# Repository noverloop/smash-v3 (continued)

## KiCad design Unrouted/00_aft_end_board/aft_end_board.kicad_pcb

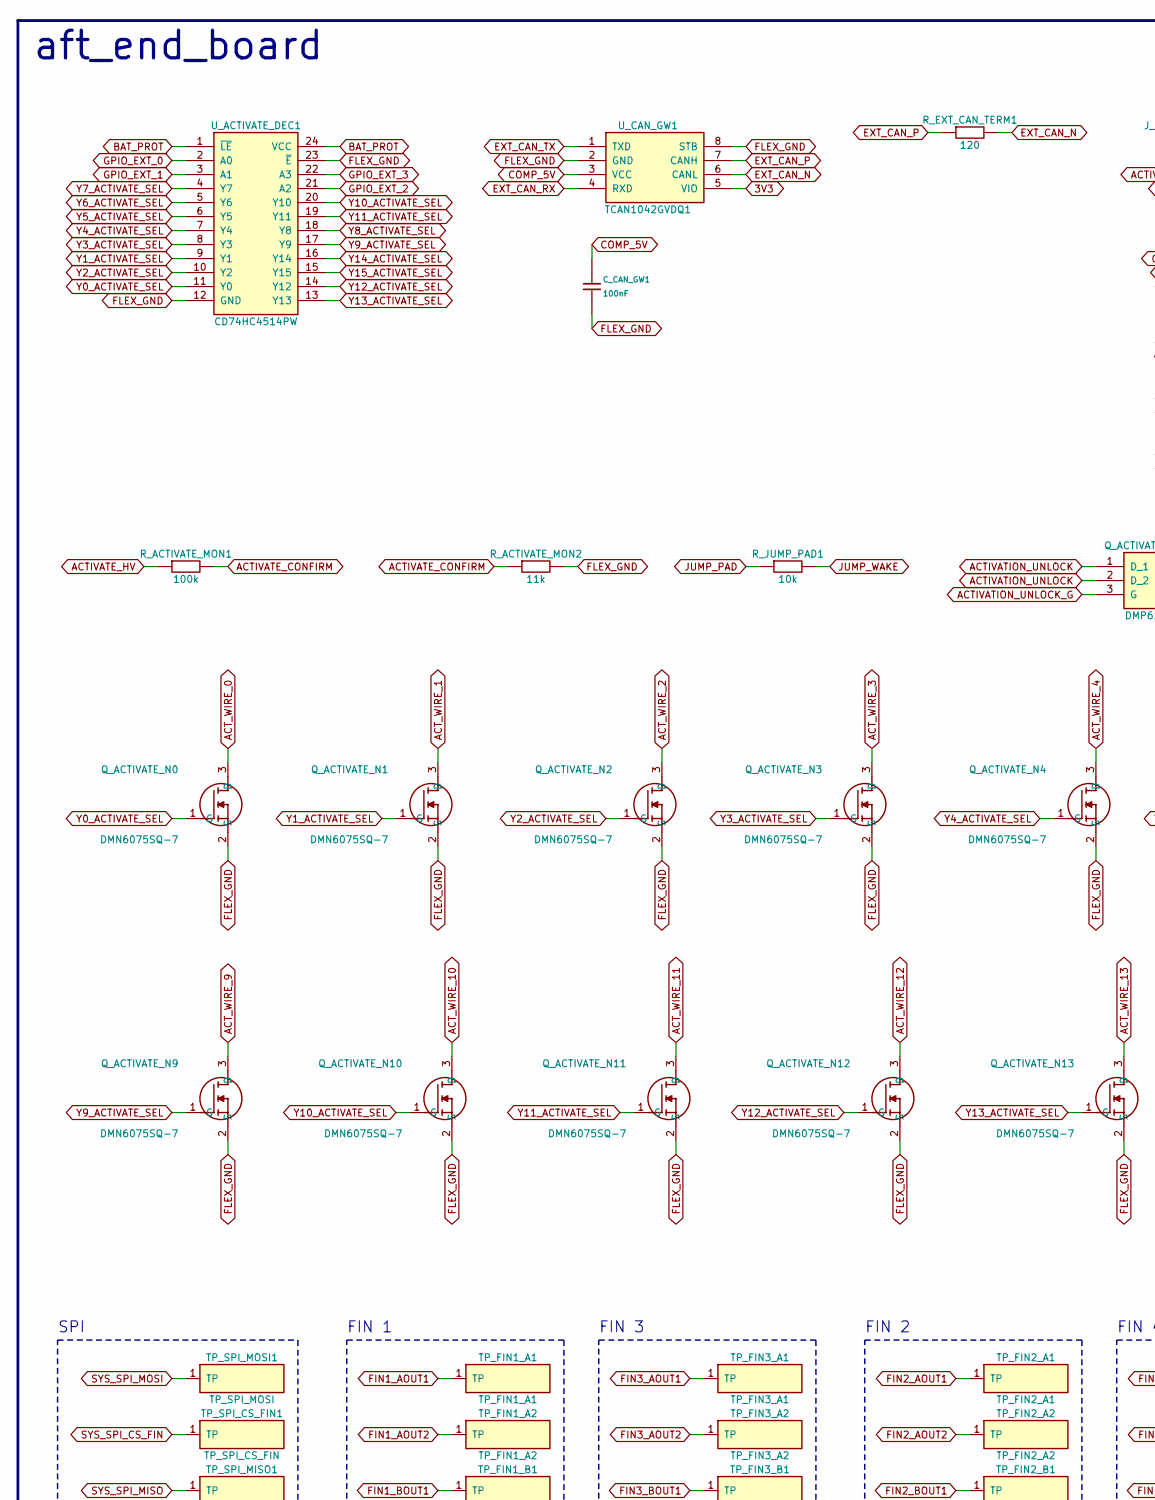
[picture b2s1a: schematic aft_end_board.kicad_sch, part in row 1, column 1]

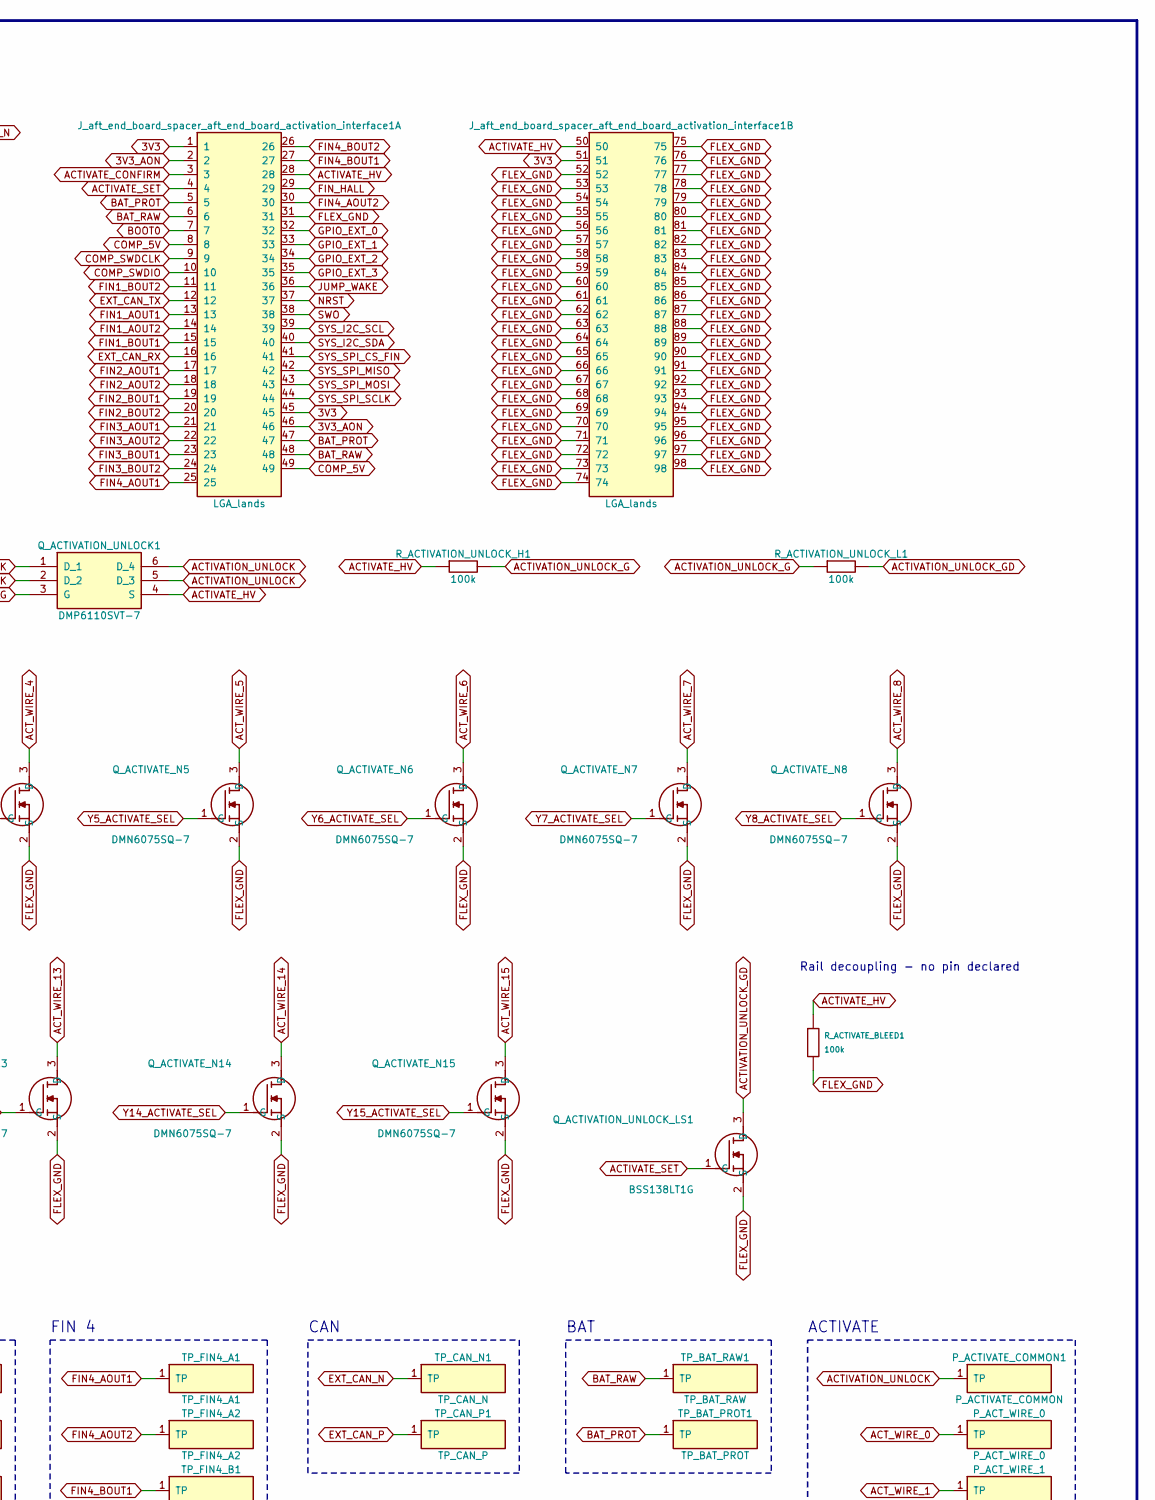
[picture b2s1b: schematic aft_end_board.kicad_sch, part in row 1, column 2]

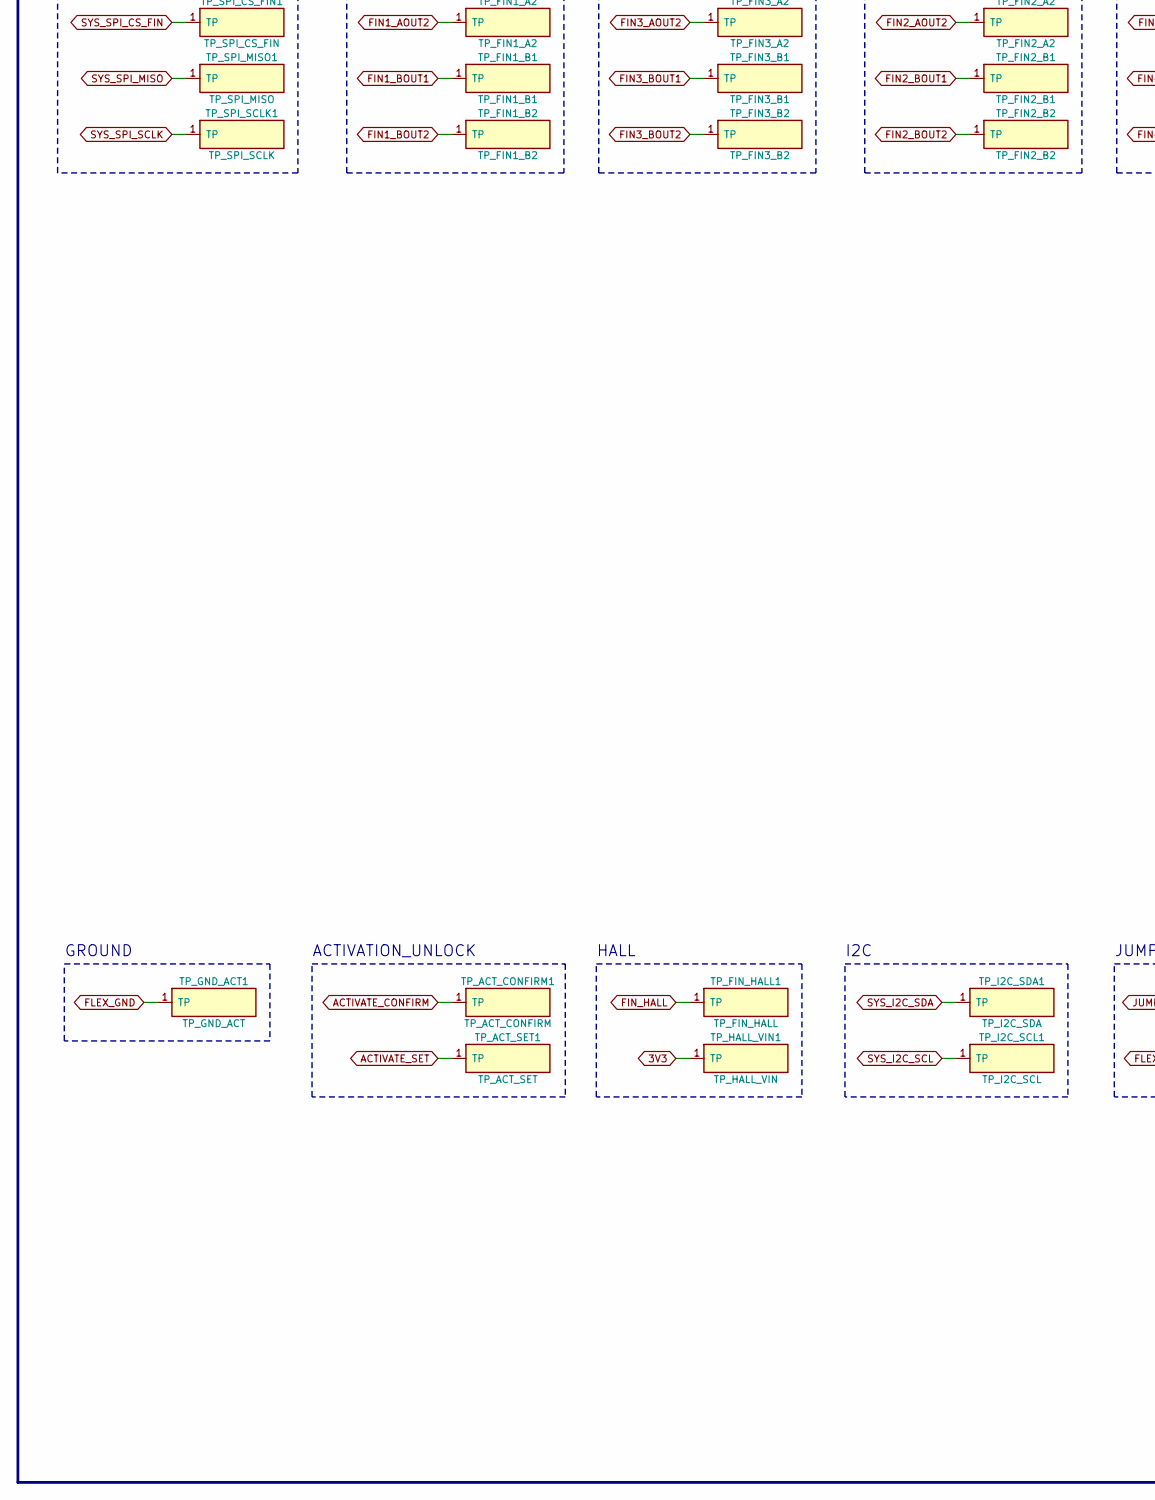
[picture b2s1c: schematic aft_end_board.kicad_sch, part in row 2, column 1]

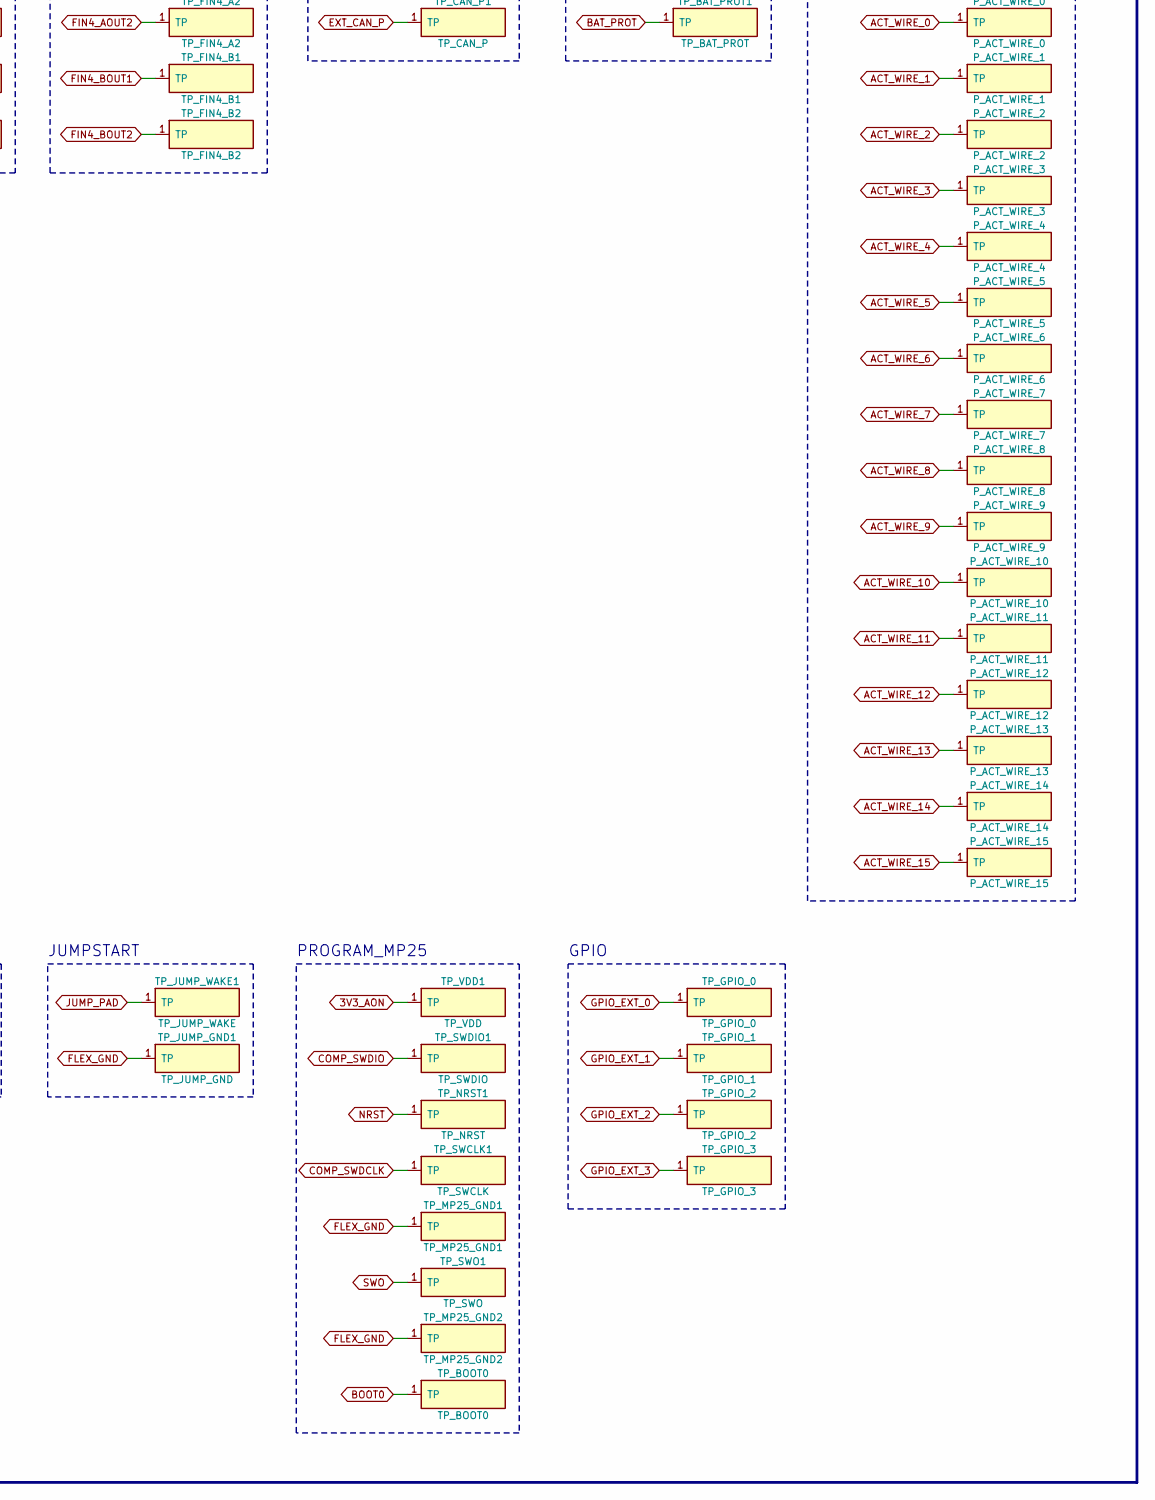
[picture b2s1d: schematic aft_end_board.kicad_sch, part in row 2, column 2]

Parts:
C_CAN_GW1: 100nF; Capacitor_SMD_C_0402_1005Metric; MPN C0402 X7R 100nF
J_aft_end_board_spacer_aft_end_board_activation_interface1: LGA_lands; J_aft_end_board_spacer_aft_end_board_activation_interface; MPN LGA_lands
P_ACTIVATE_COMMON1: P_ACTIVATE_COMMON; Pogo_Pad_D2.0mm
P_ACT_WIRE_0: P_ACT_WIRE_0; Pogo_Pad_S2.0mm
P_ACT_WIRE_1: P_ACT_WIRE_1; Pogo_Pad_D2.0mm
P_ACT_WIRE_2: P_ACT_WIRE_2; Pogo_Pad_D2.0mm
P_ACT_WIRE_3: P_ACT_WIRE_3; Pogo_Pad_D2.0mm
P_ACT_WIRE_4: P_ACT_WIRE_4; Pogo_Pad_D2.0mm
P_ACT_WIRE_5: P_ACT_WIRE_5; Pogo_Pad_D2.0mm
P_ACT_WIRE_6: P_ACT_WIRE_6; Pogo_Pad_D2.0mm
P_ACT_WIRE_7: P_ACT_WIRE_7; Pogo_Pad_D2.0mm
P_ACT_WIRE_8: P_ACT_WIRE_8; Pogo_Pad_D2.0mm
P_ACT_WIRE_9: P_ACT_WIRE_9; Pogo_Pad_D2.0mm
P_ACT_WIRE_10: P_ACT_WIRE_10; Pogo_Pad_D2.0mm
P_ACT_WIRE_11: P_ACT_WIRE_11; Pogo_Pad_D2.0mm
P_ACT_WIRE_12: P_ACT_WIRE_12; Pogo_Pad_D2.0mm
P_ACT_WIRE_13: P_ACT_WIRE_13; Pogo_Pad_D2.0mm
P_ACT_WIRE_14: P_ACT_WIRE_14; Pogo_Pad_D2.0mm
P_ACT_WIRE_15: P_ACT_WIRE_15; Pogo_Pad_D2.0mm
Q_ACTIVATE_N0, Q_ACTIVATE_N1, Q_ACTIVATE_N2, Q_ACTIVATE_N3, Q_ACTIVATE_N4, Q_ACTIVATE_N5, Q_ACTIVATE_N6, Q_ACTIVATE_N7, Q_ACTIVATE_N8, Q_ACTIVATE_N9, Q_ACTIVATE_N10, Q_ACTIVATE_N11, Q_ACTIVATE_N12, Q_ACTIVATE_N13, Q_ACTIVATE_N14, Q_ACTIVATE_N15: DMN6075SQ-7; SOT96P240X110-3N; MPN DMN6075SQ-7
Q_ACTIVATION_UNLOCK1: DMP6110SVT-7; SOT95P280X100-6N; MPN DMP6110SVT-7
Q_ACTIVATION_UNLOCK_LS1: BSS138LT1G; SOT96P237X111-3N; MPN BSS138LT1G
R_ACTIVATE_BLEED1: 100k; Resistor_SMD_R_0402_1005Metric; MPN CRCW0402 100k 1% e3
R_ACTIVATE_MON1: 100k; Resistor_SMD_R_0402_1005Metric; MPN CRCW0402 100k 1% e3
R_ACTIVATE_MON2: 11k; Resistor_SMD_R_0402_1005Metric; MPN CRCW0402 11k 1% e3
R_ACTIVATION_UNLOCK_H1: 100k; Resistor_SMD_R_0402_1005Metric; MPN CRCW0402 100k 1% e3
R_ACTIVATION_UNLOCK_L1: 100k; Resistor_SMD_R_0402_1005Metric; MPN CRCW0402 100k 1% e3
R_EXT_CAN_TERM1: 120; Resistor_SMD_R_0402_1005Metric; MPN CRCW0402 120 1% e3
R_JUMP_PAD1: 10k; Resistor_SMD_R_0402_1005Metric; MPN CRCW0402 10k 1% e3
TP_ACT_CONFIRM1: TP_ACT_CONFIRM; Pogo_Pad_S2.0mm
TP_ACT_SET1: TP_ACT_SET; Pogo_Pad_D2.0mm
TP_BAT_PROT1: TP_BAT_PROT; Pogo_Pad_D2.0mm
TP_BAT_RAW1: TP_BAT_RAW; Pogo_Pad_S2.0mm
TP_BOOT0: TP_BOOT0; Pogo_Pad_D2.0mm
TP_CAN_N1: TP_CAN_N; Pogo_Pad_S2.0mm
TP_CAN_P1: TP_CAN_P; Pogo_Pad_D2.0mm
TP_FIN1_A1: TP_FIN1_A1; Pogo_Pad_S2.0mm
TP_FIN1_A2: TP_FIN1_A2; Pogo_Pad_D2.0mm
TP_FIN1_B1: TP_FIN1_B1; Pogo_Pad_D2.0mm
TP_FIN1_B2: TP_FIN1_B2; Pogo_Pad_D2.0mm
TP_FIN2_A1: TP_FIN2_A1; Pogo_Pad_S2.0mm
TP_FIN2_A2: TP_FIN2_A2; Pogo_Pad_D2.0mm
TP_FIN2_B1: TP_FIN2_B1; Pogo_Pad_D2.0mm
TP_FIN2_B2: TP_FIN2_B2; Pogo_Pad_D2.0mm
TP_FIN3_A1: TP_FIN3_A1; Pogo_Pad_S2.0mm
TP_FIN3_A2: TP_FIN3_A2; Pogo_Pad_D2.0mm
TP_FIN3_B1: TP_FIN3_B1; Pogo_Pad_D2.0mm
TP_FIN3_B2: TP_FIN3_B2; Pogo_Pad_D2.0mm
TP_FIN4_A1: TP_FIN4_A1; Pogo_Pad_S2.0mm
TP_FIN4_A2: TP_FIN4_A2; Pogo_Pad_D2.0mm
TP_FIN4_B1: TP_FIN4_B1; Pogo_Pad_D2.0mm
TP_FIN4_B2: TP_FIN4_B2; Pogo_Pad_D2.0mm
TP_FIN_HALL1: TP_FIN_HALL; Pogo_Pad_S2.0mm
TP_GND_ACT1: TP_GND_ACT; Pogo_Pad_D2.0mm
TP_GPIO_0: TP_GPIO_0; Pogo_Pad_S2.0mm
TP_GPIO_1: TP_GPIO_1; Pogo_Pad_D2.0mm
TP_GPIO_2: TP_GPIO_2; Pogo_Pad_D2.0mm
TP_GPIO_3: TP_GPIO_3; Pogo_Pad_D2.0mm
TP_HALL_VIN1: TP_HALL_VIN; Pogo_Pad_D2.0mm
TP_I2C_SCL1: TP_I2C_SCL; Pogo_Pad_D2.0mm
TP_I2C_SDA1: TP_I2C_SDA; Pogo_Pad_S2.0mm
TP_JUMP_GND1: TP_JUMP_GND; Pogo_Pad_D2.0mm
TP_JUMP_WAKE1: TP_JUMP_WAKE; Pogo_Pad_S2.0mm
TP_MP25_GND1: TP_MP25_GND1; Pogo_Pad_D2.0mm
TP_MP25_GND2: TP_MP25_GND2; Pogo_Pad_D2.0mm
TP_NRST1: TP_NRST; Pogo_Pad_D2.0mm
TP_SPI_CS_FIN1: TP_SPI_CS_FIN; Pogo_Pad_D2.0mm
TP_SPI_MISO1: TP_SPI_MISO; Pogo_Pad_D2.0mm
TP_SPI_MOSI1: TP_SPI_MOSI; Pogo_Pad_S2.0mm
TP_SPI_SCLK1: TP_SPI_SCLK; Pogo_Pad_D2.0mm
TP_SWCLK1: TP_SWCLK; Pogo_Pad_D2.0mm
TP_SWDIO1: TP_SWDIO; Pogo_Pad_D2.0mm
TP_SWO1: TP_SWO; Pogo_Pad_D2.0mm
TP_VDD1: TP_VDD; Pogo_Pad_S2.0mm
U_ACTIVATE_DEC1: CD74HC4514PW; SOP65P640X120-24N; MPN CD74HC4514PW
U_CAN_GW1: TCAN1042GVDQ1; SOIC127P600X175-8N; MPN TCAN1042GVDQ1

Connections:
3V3: J_aft_end_board_spacer_aft_end_board_ac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.1, J_aft_end_board_spacer_aft_end_board_ac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.45, J_aft_end_board_spacer_aft_end_board_ac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.51, TP_HALL_VIN1.1, U_CAN_GW1.5 (VIO)
3V3_AON: J_aft_end_board_spacer_aft_end_board_ac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.2, J_aft_end_board_spacer_aft_end_board_ac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.46, TP_VDD1.1
ACTIVATE_CONFIRM: J_aft_end_board_spacer_aft_end_board_ac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.3, R_ACTIVATE_MON1.2, R_ACTIVATE_MON2.1, TP_ACT_CONFIRM1.1
ACTIVATE_HV: J_aft_end_board_spacer_aft_end_board_ac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.28, J_aft_end_board_spacer_aft_end_board_ac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.50, Q_ACTIVATION_UNLOCK1.4 (S), R_ACTIVATE_BLEED1.1, R_ACTIVATE_MON1.1, R_ACTIVATION_UNLOCK_H1.1
ACTIVATE_SET: J_aft_end_board_spacer_aft_end_board_ac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.4, Q_ACTIVATION_UNLOCK_LS1.1 (G), TP_ACT_SET1.1
ACTIVATION_UNLOCK: P_ACTIVATE_COMMON1.1, Q_ACTIVATION_UNLOCK1.1 (D_1), Q_ACTIVATION_UNLOCK1.2 (D_2), Q_ACTIVATION_UNLOCK1.5 (D_3), Q_ACTIVATION_UNLOCK1.6 (D_4)
ACTIVATION_UNLOCK_G: Q_ACTIVATION_UNLOCK1.3 (G), R_ACTIVATION_UNLOCK_H1.2, R_ACTIVATION_UNLOCK_L1.1
ACTIVATION_UNLOCK_GD: Q_ACTIVATION_UNLOCK_LS1.3 (D), R_ACTIVATION_UNLOCK_L1.2
ACT_WIRE_0: P_ACT_WIRE_0.1, Q_ACTIVATE_N0.3 (D)
ACT_WIRE_1: P_ACT_WIRE_1.1, Q_ACTIVATE_N1.3 (D)
ACT_WIRE_2: P_ACT_WIRE_2.1, Q_ACTIVATE_N2.3 (D)
ACT_WIRE_3: P_ACT_WIRE_3.1, Q_ACTIVATE_N3.3 (D)
ACT_WIRE_4: P_ACT_WIRE_4.1, Q_ACTIVATE_N4.3 (D)
ACT_WIRE_5: P_ACT_WIRE_5.1, Q_ACTIVATE_N5.3 (D)
ACT_WIRE_6: P_ACT_WIRE_6.1, Q_ACTIVATE_N6.3 (D)
ACT_WIRE_7: P_ACT_WIRE_7.1, Q_ACTIVATE_N7.3 (D)
ACT_WIRE_8: P_ACT_WIRE_8.1, Q_ACTIVATE_N8.3 (D)
ACT_WIRE_9: P_ACT_WIRE_9.1, Q_ACTIVATE_N9.3 (D)
ACT_WIRE_10: P_ACT_WIRE_10.1, Q_ACTIVATE_N10.3 (D)
ACT_WIRE_11: P_ACT_WIRE_11.1, Q_ACTIVATE_N11.3 (D)
ACT_WIRE_12: P_ACT_WIRE_12.1, Q_ACTIVATE_N12.3 (D)
ACT_WIRE_13: P_ACT_WIRE_13.1, Q_ACTIVATE_N13.3 (D)
ACT_WIRE_14: P_ACT_WIRE_14.1, Q_ACTIVATE_N14.3 (D)
ACT_WIRE_15: P_ACT_WIRE_15.1, Q_ACTIVATE_N15.3 (D)
BAT_PROT: J_aft_end_board_spacer_aft_end_board_ac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.5, J_aft_end_board_spacer_aft_end_board_ac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.47, TP_BAT_PROT1.1, U_ACTIVATE_DEC1.1 (~LE), U_ACTIVATE_DEC1.24 (VCC)
BAT_RAW: J_aft_end_board_spacer_aft_end_board_ac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.6, J_aft_end_board_spacer_aft_end_board_ac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.48, TP_BAT_RAW1.1
BOOT0: J_aft_end_board_spacer_aft_end_board_ac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.7, TP_BOOT0.1
COMP_5V: C_CAN_GW1.1, J_aft_end_board_spacer_aft_end_board_ac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.8, J_aft_end_board_spacer_aft_end_board_ac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.49, U_CAN_GW1.3 (VCC)
COMP_SWDCLK: J_aft_end_board_spacer_aft_end_board_ac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.9, TP_SWCLK1.1
COMP_SWDIO: J_aft_end_board_spacer_aft_end_board_ac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.10, TP_SWDIO1.1
EXT_CAN_N: R_EXT_CAN_TERM1.2, TP_CAN_N1.1, U_CAN_GW1.6 (CANL)
EXT_CAN_P: R_EXT_CAN_TERM1.1, TP_CAN_P1.1, U_CAN_GW1.7 (CANH)
EXT_CAN_RX: J_aft_end_board_spacer_aft_end_board_ac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.16, U_CAN_GW1.4 (RXD)
EXT_CAN_TX: J_aft_end_board_spacer_aft_end_board_ac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.12, U_CAN_GW1.1 (TXD)
FIN1_AOUT1: J_aft_end_board_spacer_aft_end_board_ac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.13, TP_FIN1_A1.1
FIN1_AOUT2: J_aft_end_board_spacer_aft_end_board_ac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.14, TP_FIN1_A2.1
FIN1_BOUT1: J_aft_end_board_spacer_aft_end_board_ac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.15, TP_FIN1_B1.1
FIN1_BOUT2: J_aft_end_board_spacer_aft_end_board_ac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.11, TP_FIN1_B2.1
FIN2_AOUT1: J_aft_end_board_spacer_aft_end_board_ac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.17, TP_FIN2_A1.1
FIN2_AOUT2: J_aft_end_board_spacer_aft_end_board_ac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.18, TP_FIN2_A2.1
FIN2_BOUT1: J_aft_end_board_spacer_aft_end_board_ac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.19, TP_FIN2_B1.1
FIN2_BOUT2: J_aft_end_board_spacer_aft_end_board_ac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.20, TP_FIN2_B2.1
FIN3_AOUT1: J_aft_end_board_spacer_aft_end_board_ac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.21, TP_FIN3_A1.1
FIN3_AOUT2: J_aft_end_board_spacer_aft_end_board_ac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.22, TP_FIN3_A2.1
FIN3_BOUT1: J_aft_end_board_spacer_aft_end_board_ac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.23, TP_FIN3_B1.1
FIN3_BOUT2: J_aft_end_board_spacer_aft_end_board_ac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.24, TP_FIN3_B2.1
FIN4_AOUT1: J_aft_end_board_spacer_aft_end_board_ac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.25, TP_FIN4_A1.1
FIN4_AOUT2: J_aft_end_board_spacer_aft_end_board_ac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.30, TP_FIN4_A2.1
FIN4_BOUT1: J_aft_end_board_spacer_aft_end_board_ac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.27, TP_FIN4_B1.1
FIN4_BOUT2: J_aft_end_board_spacer_aft_end_board_ac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.26, TP_FIN4_B2.1
FIN_HALL: J_aft_end_board_spacer_aft_end_board_ac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.29, TP_FIN_HALL1.1
FLEX_GND: C_CAN_GW1.2, J_aft_end_board_spacer_aft_end_board_ac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.31, J_aft_end_board_spacer_aft_end_board_ac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.52, J_aft_end_board_spacer_aft_end_board_ac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.53, J_aft_end_board_spacer_aft_end_board_ac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.54, J_aft_end_board_spacer_aft_end_board_ac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.55, J_aft_end_board_spacer_aft_end_board_ac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.56, J_aft_end_board_spacer_aft_end_board_ac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.57, J_aft_end_board_spacer_aft_end_board_ac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.58, J_aft_end_board_spacer_aft_end_board_ac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.59, J_aft_end_board_spacer_aft_end_board_ac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.60, J_aft_end_board_spacer_aft_end_board_ac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.61, J_aft_end_board_spacer_aft_end_board_ac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.62, J_aft_end_board_spacer_aft_end_board_ac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.63, J_aft_end_board_spacer_aft_end_board_ac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.64, J_aft_end_board_spacer_aft_end_board_ac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.65, J_aft_end_board_spacer_aft_end_board_ac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.66, J_aft_end_board_spacer_aft_end_board_ac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.67, J_aft_end_board_spacer_aft_end_board_ac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.68, J_aft_end_board_spacer_aft_end_board_ac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.69, J_aft_end_board_spacer_aft_end_board_ac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.70, J_aft_end_board_spacer_aft_end_board_ac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.71, J_aft_end_board_spacer_aft_end_board_ac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.72, J_aft_end_board_spacer_aft_end_board_ac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.73, J_aft_end_board_spacer_aft_end_board_ac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.74, J_aft_end_board_spacer_aft_end_board_ac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.75, J_aft_end_board_spacer_aft_end_board_ac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.76, J_aft_end_board_spacer_aft_end_board_ac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.77, J_aft_end_board_spacer_aft_end_board_ac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.78, J_aft_end_board_spacer_aft_end_board_ac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.79, J_aft_end_board_spacer_aft_end_board_ac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.80, J_aft_end_board_spacer_aft_end_board_ac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.81, J_aft_end_board_spacer_aft_end_board_ac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.82, J_aft_end_board_spacer_aft_end_board_ac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.83, J_aft_end_board_spacer_aft_end_board_ac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.84, J_aft_end_board_spacer_aft_end_board_ac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.85, J_aft_end_board_spacer_aft_end_board_ac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.86, J_aft_end_board_spacer_aft_end_board_ac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.87, J_aft_end_board_spacer_aft_end_board_ac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.88, J_aft_end_board_spacer_aft_end_board_ac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.89, J_aft_end_board_spacer_aft_end_board_ac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.90, J_aft_end_board_spacer_aft_end_board_ac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.91, J_aft_end_board_spacer_aft_end_board_ac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.92, J_aft_end_board_spacer_aft_end_board_ac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.93, J_aft_end_board_spacer_aft_end_board_ac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.94, J_aft_end_board_spacer_aft_end_board_ac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.95, J_aft_end_board_spacer_aft_end_board_ac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.96, J_aft_end_board_spacer_aft_end_board_ac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.97, J_aft_end_board_spacer_aft_end_board_ac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.98, Q_ACTIVATE_N0.2 (S), Q_ACTIVATE_N1.2 (S), Q_ACTIVATE_N2.2 (S), Q_ACTIVATE_N3.2 (S), Q_ACTIVATE_N4.2 (S), Q_ACTIVATE_N5.2 (S), Q_ACTIVATE_N6.2 (S), Q_ACTIVATE_N7.2 (S), Q_ACTIVATE_N8.2 (S), Q_ACTIVATE_N9.2 (S), Q_ACTIVATE_N10.2 (S), Q_ACTIVATE_N11.2 (S), Q_ACTIVATE_N12.2 (S), Q_ACTIVATE_N13.2 (S), Q_ACTIVATE_N14.2 (S), Q_ACTIVATE_N15.2 (S), Q_ACTIVATION_UNLOCK_LS1.2 (S), R_ACTIVATE_BLEED1.2, R_ACTIVATE_MON2.2, TP_GND_ACT1.1, TP_JUMP_GND1.1, TP_MP25_GND1.1, TP_MP25_GND2.1, U_ACTIVATE_DEC1.12 (GND), U_ACTIVATE_DEC1.23 (~E), U_CAN_GW1.2 (GND), U_CAN_GW1.8 (STB)
GPIO_EXT_0: J_aft_end_board_spacer_aft_end_board_ac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.32, TP_GPIO_0.1, U_ACTIVATE_DEC1.2 (A0)
GPIO_EXT_1: J_aft_end_board_spacer_aft_end_board_ac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.33, TP_GPIO_1.1, U_ACTIVATE_DEC1.3 (A1)
GPIO_EXT_2: J_aft_end_board_spacer_aft_end_board_ac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.34, TP_GPIO_2.1, U_ACTIVATE_DEC1.21 (A2)
GPIO_EXT_3: J_aft_end_board_spacer_aft_end_board_ac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.35, TP_GPIO_3.1, U_ACTIVATE_DEC1.22 (A3)
JUMP_PAD: R_JUMP_PAD1.1, TP_JUMP_WAKE1.1
JUMP_WAKE: J_aft_end_board_spacer_aft_end_board_ac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.36, R_JUMP_PAD1.2
NRST: J_aft_end_board_spacer_aft_end_board_ac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.37, TP_NRST1.1
SWO: J_aft_end_board_spacer_aft_end_board_ac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.38, TP_SWO1.1
SYS_I2C_SCL: J_aft_end_board_spacer_aft_end_board_ac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.39, TP_I2C_SCL1.1
SYS_I2C_SDA: J_aft_end_board_spacer_aft_end_board_ac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.40, TP_I2C_SDA1.1
SYS_SPI_CS_FIN: J_aft_end_board_spacer_aft_end_board_ac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.41, TP_SPI_CS_FIN1.1
SYS_SPI_MISO: J_aft_end_board_spacer_aft_end_board_ac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.42, TP_SPI_MISO1.1
SYS_SPI_MOSI: J_aft_end_board_spacer_aft_end_board_ac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.43, TP_SPI_MOSI1.1
SYS_SPI_SCLK: J_aft_end_board_spacer_aft_end_board_ac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.44, TP_SPI_SCLK1.1
Y0_ACTIVATE_SEL: Q_ACTIVATE_N0.1 (G), U_ACTIVATE_DEC1.11 (Y0)
Y1_ACTIVATE_SEL: Q_ACTIVATE_N1.1 (G), U_ACTIVATE_DEC1.9 (Y1)
Y2_ACTIVATE_SEL: Q_ACTIVATE_N2.1 (G), U_ACTIVATE_DEC1.10 (Y2)
Y3_ACTIVATE_SEL: Q_ACTIVATE_N3.1 (G), U_ACTIVATE_DEC1.8 (Y3)
Y4_ACTIVATE_SEL: Q_ACTIVATE_N4.1 (G), U_ACTIVATE_DEC1.7 (Y4)
Y5_ACTIVATE_SEL: Q_ACTIVATE_N5.1 (G), U_ACTIVATE_DEC1.6 (Y5)
Y6_ACTIVATE_SEL: Q_ACTIVATE_N6.1 (G), U_ACTIVATE_DEC1.5 (Y6)
Y7_ACTIVATE_SEL: Q_ACTIVATE_N7.1 (G), U_ACTIVATE_DEC1.4 (Y7)
Y8_ACTIVATE_SEL: Q_ACTIVATE_N8.1 (G), U_ACTIVATE_DEC1.18 (Y8)
Y9_ACTIVATE_SEL: Q_ACTIVATE_N9.1 (G), U_ACTIVATE_DEC1.17 (Y9)
Y10_ACTIVATE_SEL: Q_ACTIVATE_N10.1 (G), U_ACTIVATE_DEC1.20 (Y10)
Y11_ACTIVATE_SEL: Q_ACTIVATE_N11.1 (G), U_ACTIVATE_DEC1.19 (Y11)
Y12_ACTIVATE_SEL: Q_ACTIVATE_N12.1 (G), U_ACTIVATE_DEC1.14 (Y12)
Y13_ACTIVATE_SEL: Q_ACTIVATE_N13.1 (G), U_ACTIVATE_DEC1.13 (Y13)
Y14_ACTIVATE_SEL: Q_ACTIVATE_N14.1 (G), U_ACTIVATE_DEC1.16 (Y14)
Y15_ACTIVATE_SEL: Q_ACTIVATE_N15.1 (G), U_ACTIVATE_DEC1.15 (Y15)

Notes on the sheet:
aft_end_board
Rail decoupling - no pin declared
SPI
FIN 1
FIN 3
FIN 2
FIN 4
CAN
BAT
ACTIVATE
GROUND
ACTIVATION_UNLOCK
HALL
I2C
JUMPSTART
PROGRAM_MP25
GPIO

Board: 14 copper layers, 91 parts (62 on the bottom side), 82 nets, no tracks yet.
